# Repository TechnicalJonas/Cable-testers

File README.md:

# Cable-testers
Creating cable testers at work to efficiently and quickly test cables and determine with wires have disconnected to the connector.

This project is a one of many tester to be built to test and very the continuity of test cables for onw of the assemblies.
manually checking each pins takes minutes to complete and creating this tester will make our ob easier.

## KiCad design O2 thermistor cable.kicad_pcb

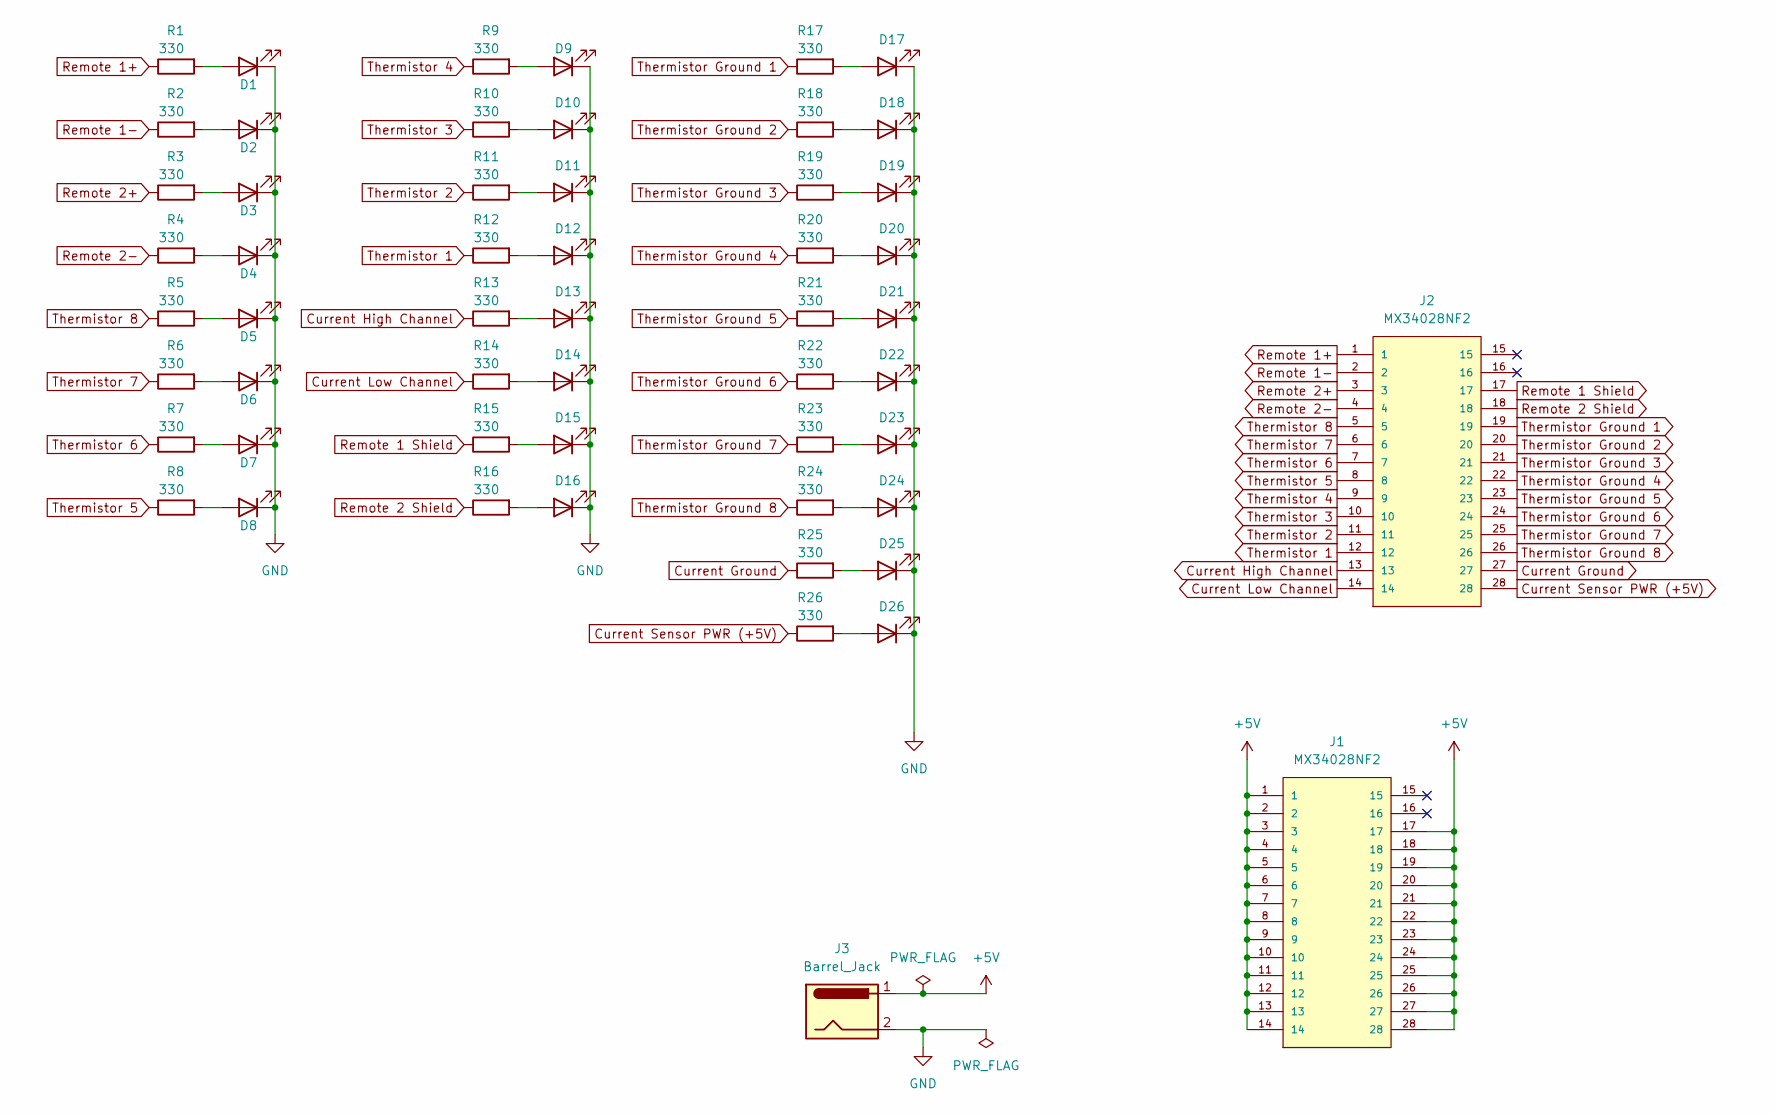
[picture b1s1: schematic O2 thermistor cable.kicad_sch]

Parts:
D1, D2, D3, D4, D5, D6, D7, D8, D9, D10, D11, D12, D13, D14, D15, D16, D17, D18, D19, D20, D21, D22, D23, D24, D25, D26: LED; LED_D3.0mm
J1, J2: MX34028NF2; JAE_MX34028NF2
J3: Barrel_Jack; BarrelJack_GCT_DCJ200-10-A_Horizontal
R1, R2, R3, R4, R5, R6, R7, R8, R9, R10, R11, R12, R13, R14, R15, R16, R17, R18, R19, R20, R21, R22, R23, R24, R25, R26: 330; R_Axial_DIN0204_L3.6mm_D1.6mm_P1.90mm_Vertical

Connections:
+5V: J1.1, J1.2, J1.3, J1.4, J1.5, J1.6, J1.7, J1.8, J1.9, J1.10, J1.11, J1.12, J1.13, J1.14, J1.17, J1.18, J1.19, J1.20, J1.21, J1.22, J1.23, J1.24, J1.25, J1.26, J1.27, J1.28, J3.1
Current Ground: J2.27, R25.1
Current High Channel: J2.13, R13.1
Current Low Channel: J2.14, R14.1
Current Sensor PWR (+5V): J2.28, R26.1
GND: D1.1 (K), D2.1 (K), D3.1 (K), D4.1 (K), D5.1 (K), D6.1 (K), D7.1 (K), D8.1 (K), D9.1 (K), D10.1 (K), D11.1 (K), D12.1 (K), D13.1 (K), D14.1 (K), D15.1 (K), D16.1 (K), D17.1 (K), D18.1 (K), D19.1 (K), D20.1 (K), D21.1 (K), D22.1 (K), D23.1 (K), D24.1 (K), D25.1 (K), D26.1 (K), J3.2
unnamed: D1.2 (A), R1.2
unnamed: D2.2 (A), R2.2
unnamed: D3.2 (A), R3.2
unnamed: D4.2 (A), R4.2
unnamed: D5.2 (A), R5.2
unnamed: D6.2 (A), R6.2
unnamed: D7.2 (A), R7.2
unnamed: D8.2 (A), R8.2
unnamed: D9.2 (A), R9.2
unnamed: D10.2 (A), R10.2
unnamed: D11.2 (A), R11.2
unnamed: D12.2 (A), R12.2
unnamed: D13.2 (A), R13.2
unnamed: D14.2 (A), R14.2
unnamed: D15.2 (A), R15.2
unnamed: D16.2 (A), R16.2
unnamed: D17.2 (A), R17.2
unnamed: D18.2 (A), R18.2
unnamed: D19.2 (A), R19.2
unnamed: D20.2 (A), R20.2
unnamed: D21.2 (A), R21.2
unnamed: D22.2 (A), R22.2
unnamed: D23.2 (A), R23.2
unnamed: D24.2 (A), R24.2
unnamed: D25.2 (A), R25.2
unnamed: D26.2 (A), R26.2
Remote 1 Shield: J2.17, R15.1
Remote 1+: J2.1, R1.1
Remote 1-: J2.2, R2.1
Remote 2 Shield: J2.18, R16.1
Remote 2+: J2.3, R3.1
Remote 2-: J2.4, R4.1
Thermistor 1: J2.12, R12.1
Thermistor 2: J2.11, R11.1
Thermistor 3: J2.10, R10.1
Thermistor 4: J2.9, R9.1
Thermistor 5: J2.8, R8.1
Thermistor 6: J2.7, R7.1
Thermistor 7: J2.6, R6.1
Thermistor 8: J2.5, R5.1
Thermistor Ground 1: J2.19, R17.1
Thermistor Ground 2: J2.20, R18.1
Thermistor Ground 3: J2.21, R19.1
Thermistor Ground 4: J2.22, R20.1
Thermistor Ground 5: J2.23, R21.1
Thermistor Ground 6: J2.24, R22.1
Thermistor Ground 7: J2.25, R23.1
Thermistor Ground 8: J2.26, R24.1

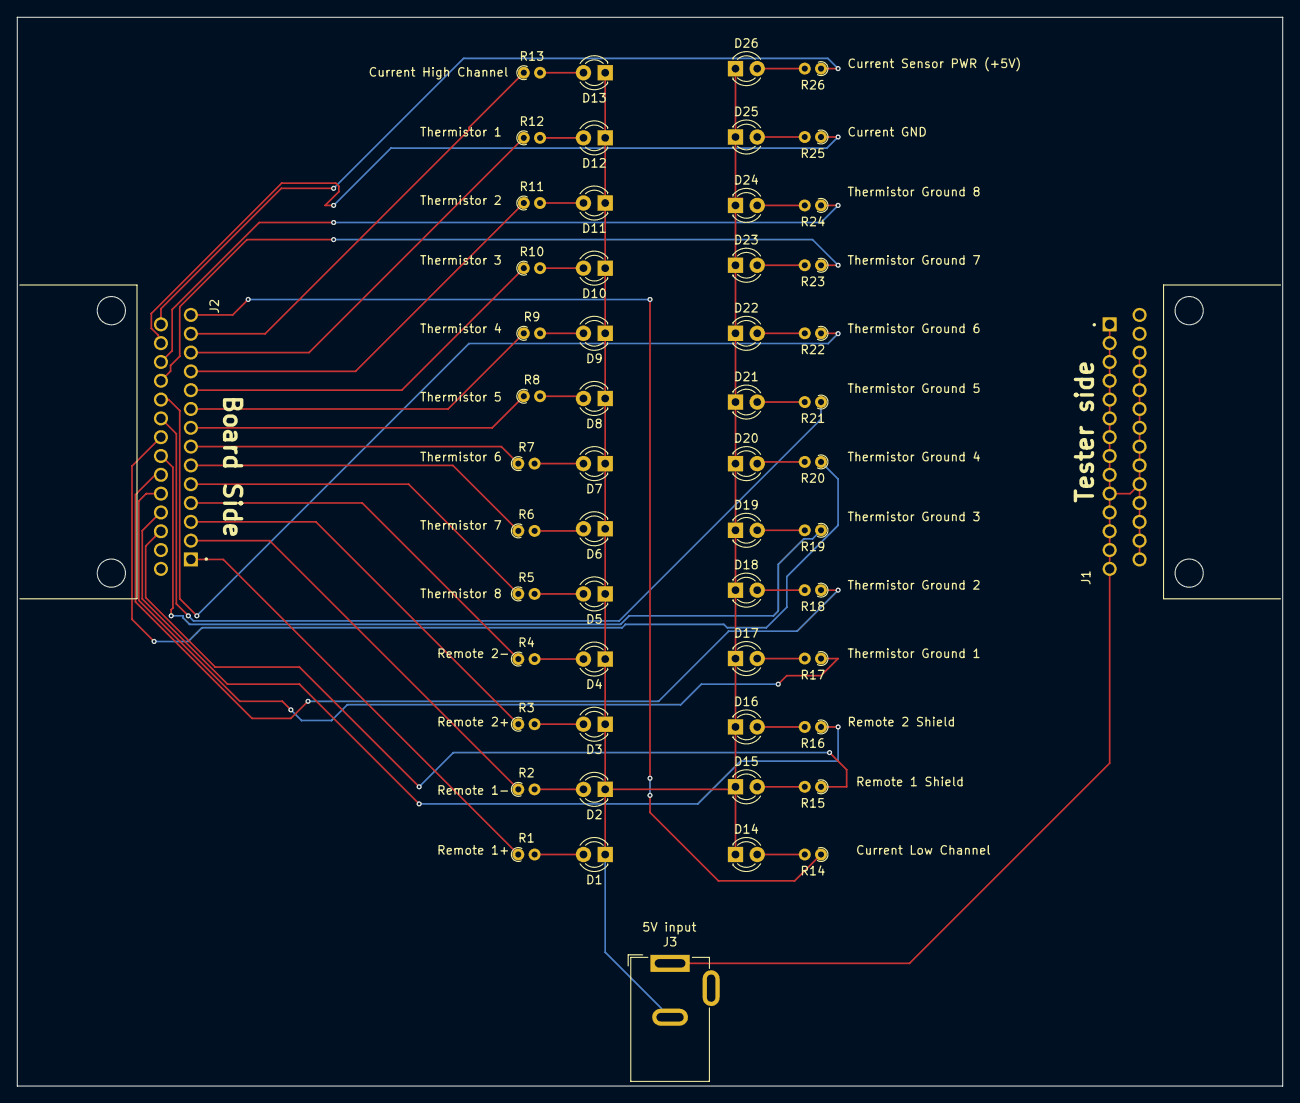
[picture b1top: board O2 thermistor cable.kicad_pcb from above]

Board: 2 copper layers, 148.0 x 125.0 mm, 55 parts (0 on the bottom side), 54 nets.

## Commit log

2023-08-23 adding schematic, drawing, and gerber files
